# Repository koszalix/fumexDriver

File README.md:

# Fumex Driver
PWM fan speed regulator for the [Fumex Project](https://github.com/koszalix/Fumex)

# Licensing

This project is published under the Apache-2.0 license.

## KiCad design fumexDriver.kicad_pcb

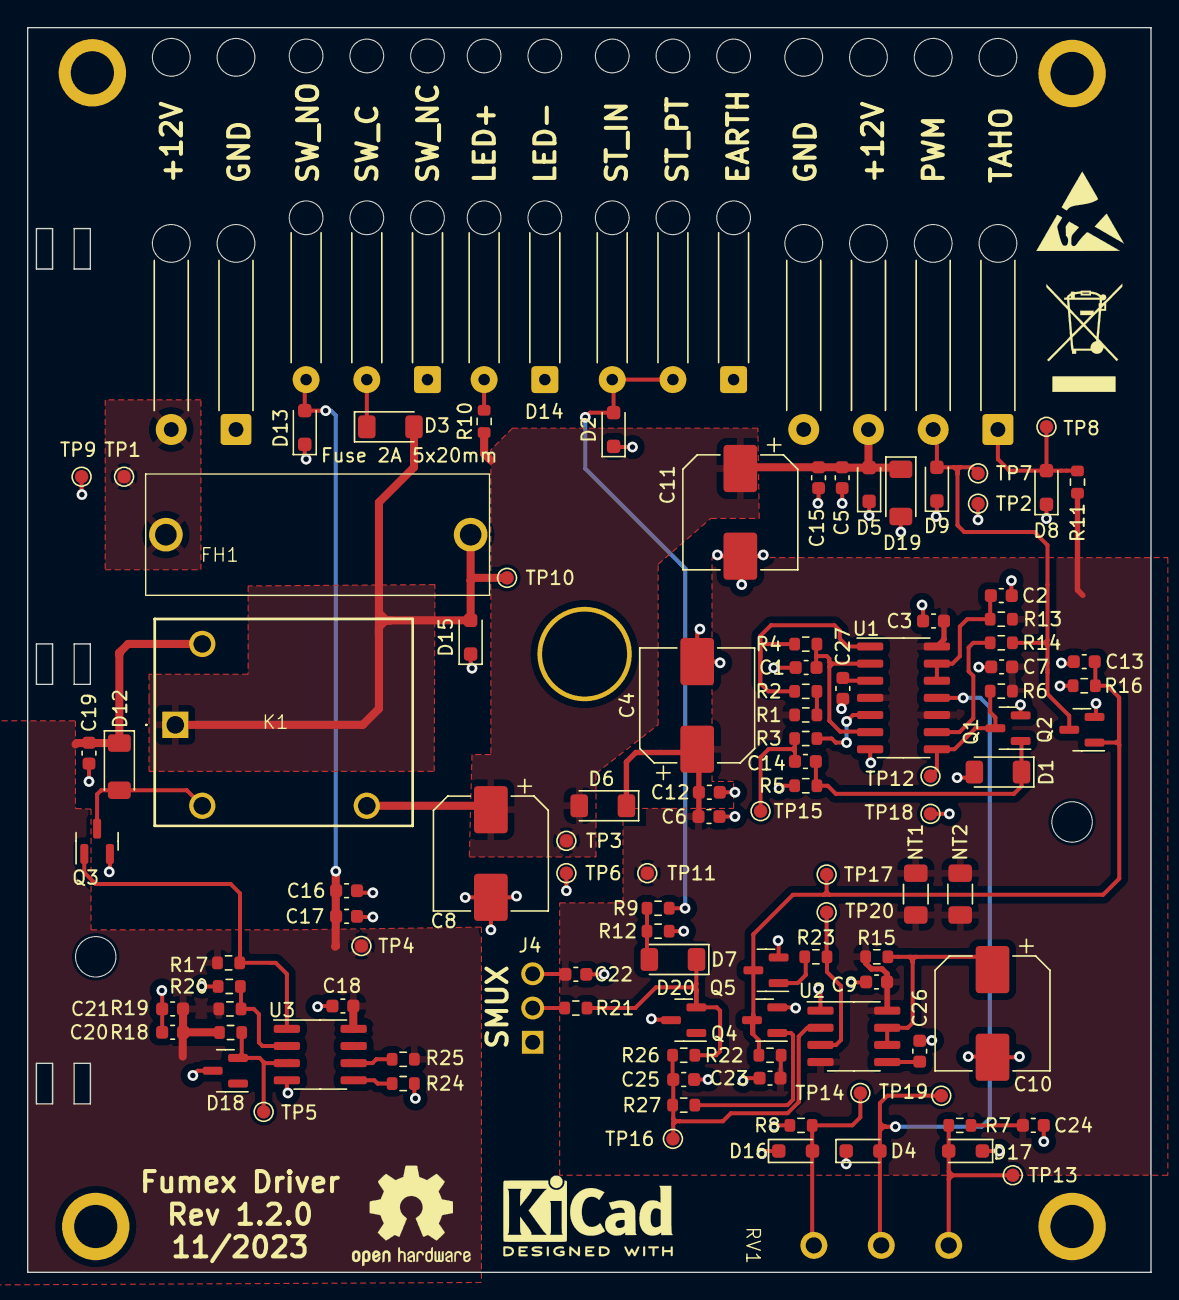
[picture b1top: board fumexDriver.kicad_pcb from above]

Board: 2 copper layers, 83.3 x 92.3 mm, 116 parts (0 on the bottom side), 40 nets.

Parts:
C1, C2: 47n; C_0603_1608Metric
C3, C6, C7, C9, C15, C17, C18, C19, C20, C22, C23, C24, C26, C27: 100n; C_0603_1608Metric
C4, C8, C10, C11: 220u; CP_Elec_8x10
C5, C12, C16, C21, C25: 1u; C_0603_1608Metric
C13, C14: 1n; C_0603_1608Metric
D1, D3, D6, D7, D12, D19: LL103A; D_MiniMELF
D2, D4, D5, D8, D9, D13, D15, D16, D17: ESD3B15WS; D_SOD-323_HandSoldering
D14: LED; SolderWire-0.25sqmm_1x02_P4.5mm_D0.65mm_OD2mm_Relief2x
D18, D20: 2BZX84Cxx; SOT-23
FH1: 503.400; ESKA_503.400
H1, H2: MountingHole; MountingHole_3mm
J1: PWR; SolderWire-0.5sqmm_1x02_P4.8mm_D0.9mm_OD2.3mm_Relief2x
J2: FAN; SolderWire-0.5sqmm_1x04_P4.8mm_D0.9mm_OD2.3mm_Relief2x
J3: STAND; SolderWire-0.25sqmm_1x03_P4.5mm_D0.65mm_OD2mm_Relief2x
J4: 68000-103HLF; Amphenol_68000-103HLF
K1: AZ943-1AH-12DE; Zettler_AZ943
MC1: KRADEX Z5; z5
NT1, NT2: NetTie_2; R_1206_3216Metric_Pad1.30x1.75mm_HandSolder
Q1, Q3, Q4, Q5: BC847; SOT-23
Q2: 2N7002; SOT-23
R1, R2, R3, R4, R5, R6, R9, R11, R13, R14, R17, R18, R19, R20, R21, R22, R23, R27: 3k3; R_0603_1608Metric
R7, R10: 680R; R_0603_1608Metric
R8: 100R; R_0603_1608Metric
R12, R15, R16: 100k; R_0603_1608Metric
R24, R25: 10k; R_0603_1608Metric
R26: 47k; R_0603_1608Metric
REF100: WEEE-Logo_5.6x8mm_SilkScreen
REF101: OSHW-Logo2_9.8x8mm_SilkScreen
REF102: KiCad-Logo2_5mm_SilkScreen
RV1: 10k; SR_PASSIVES_R16148
SW1: LC1258EENP; SolderWire-0.25sqmm_1x03_P4.5mm_D0.65mm_OD2mm_Relief2x
TP1, TP3, TP10: +12V; TestPoint_Pad_D1.0mm
TP2, TP6, TP9: GND; TestPoint_Pad_D1.0mm
TP4, TP5, TP11: +12VA; TestPoint_Pad_D1.0mm
TP7: TestPoint_Pad_D1.0mm
TP8: TACHO; TestPoint_Pad_D1.0mm
TP12, TP13, TP14, TP15, TP16, TP17, TP18, TP19, TP20: TestPoint_Pad_D1.0mm
U1: NE556; SOIC-14_3.9x8.7mm_P1.27mm
U2: NE555D; SOIC-8_3.9x4.9mm_P1.27mm
U3: LM393; SOIC-8_3.9x4.9mm_P1.27mm

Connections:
+12L: D3.2 (A), D15.2 (A2), FH1.2, K1.13, TP10.1
+12P: C16.1, C17.1, C18.1, C19.1, C20.1, C21.1, D12.1 (K), D13.2 (A2), K1.A1, R17.2, R18.2, R19.2, R25.1, SW1.3 (C), TP4.1, U3.8 (V+)
+12V: C5.1, C8.1, C11.1, C15.1, D5.2 (A2), D6.2 (A), D19.1 (K), J2.3, K1.14, R10.1, TP3.1
+12VA: C3.1, C4.1, C6.1, C7.1, C9.1, C12.1, C22.1, C23.1, C24.1, D6.1 (K), J4.3, NT1.1, NT1.2, NT2.1, NT2.2, R1.1, R6.2, R7.1, R11.2, R13.2, R15.1, R22.1, TP11.1, U1.4 (R), U1.10 (R), U1.14 (VCC), U2.4 (R), U2.8 (VCC)
/PWM generator/F_{FBK}: D8.2 (A2), J2.1, R11.1, TP8.1
/PWM generator/F_{PWM}: D9.2 (A2), J2.2, Q2.3 (D), R14.1, TP7.1
GND: C1.2, C2.2, C3.2, C4.2, C5.2, C6.2, C7.2, C8.2, C9.2, C10.2, C11.2, C12.2, C13.1, C15.2, C16.2, C17.2, C18.2, C19.2, C20.2, C21.2, C22.2, C23.2, C24.2, C25.2, C26.2, C27.2, D1.2 (A), D2.1 (A1), D4.1 (A1), D5.1 (A1), D8.1 (A1), D9.1 (A1), D13.1 (A1), D14.1 (K), D15.1 (A1), D16.1 (A1), D17.1 (A1), D18.3 (A), D19.2 (A), D20.3 (A), J1.1, J2.4, J3.1, J4.1, Q1.2 (E), Q2.2 (S), Q3.2 (E), Q4.2 (E), Q5.2 (E), R5.1, R8.2, R12.2, R16.2, R20.1, R24.1, TP2.1, TP6.1, TP9.1, TP18.1, U1.7 (GND), U2.1 (GND), U3.4 (V-)
unnamed: C14.1, R3.2, TP15.1
unnamed: C14.2, D1.1 (K), Q1.1 (B), R5.2
unnamed: D2.2 (A2), J3.2, J3.3, R9.2
unnamed: D3.1 (K), SW1.2 (B)
unnamed: D4.2 (A2), RV1.2, TP19.1, U1.11 (CV)
unnamed: D7.2 (A), R9.1, R12.1
unnamed: D7.1 (K), D20.2 (K), R21.1, R26.1
unnamed: D12.2 (A), K1.A2, Q3.3 (C)
unnamed: D14.2 (A), R10.2
unnamed: D16.2 (A2), R8.1, RV1.1, TP14.1
unnamed: D17.2 (A2), R7.2, RV1.3, TP13.1
unnamed: FH1.1, J1.2, TP1.1
unnamed: J4.2, R21.2
unnamed: Q1.3 (C), R6.1, TP12.1, U1.8 (TR)
unnamed: C13.2, Q2.1 (G), Q4.3 (C), Q5.3 (C), R16.1, R22.2, TP17.1
unnamed: Q3.1 (B), R17.1, U3.1
unnamed: Q4.1 (B), R27.1
unnamed: Q5.1 (B), R23.1
unnamed: R1.2, R2.1
unnamed: C27.1, U1.3 (CV)
unnamed: R2.2, R4.1, U1.1 (DIS)
unnamed: R3.1, U1.5 (Q)
unnamed: C1.1, R4.2, U1.2 (THR), U1.6 (TR)
unnamed: C2.1, R13.1, U1.12 (THR), U1.13 (DIS)
unnamed: R14.2, U1.9 (Q)
unnamed: C26.1, U2.5 (CV)
unnamed: C10.1, R15.2, U2.6 (THR), U2.7 (DIS)
unnamed: R23.2, TP20.1, U2.3 (Q)
unnamed: C25.1, R26.2, R27.2, TP16.1, U2.2 (TR)
unnamed: D18.2 (K), R18.1, TP5.1, U3.3 (+)
unnamed: R19.1, R20.2, U3.2 (-)
unnamed: R24.2, U3.5 (+)
unnamed: R25.2, U3.6 (-)

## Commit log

2023-11-21 Revison 1.0.0 release
2023-11-22 Add Licensing to README.md
2023-11-22 Release 1.0.0
2023-11-22 Release 1.1.0
2023-12-29 Release 1.2.0
2024-01-14 Remove C25 from schematic
2024-01-14 Remove R26 from schematic
2024-01-14 Remove D20 from schematic
2024-06-05 Fix U2 treshold circuit
